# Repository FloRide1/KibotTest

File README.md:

# Kibot Test
## By Florian "FloRide" Reimat

## About
This repo is a test about a Kicad Plugins named "[KiBot](https://github.com/INTI-CMNB/kibot)", an all in one plugins made for automatically generate export files like BOM / Cost / Gerber / etc... It also handle CI / CD with Github / Gitlab.

## Images:
### Schematic:

### PCB:
| Front | Bottom |
:------:|:-------:
|| |
### 3D:
| Front | Bottom |
:------:|:-------:
|| |
| Tilted 1 | Tilted 2 |
|  |  |

## Others:
- [Interactive BOM](Export/ibom/KibotTest-ibom.html)
- [BOM](Export/bom/KibotTest-bom.csv)
- [Cost](Export/cost/KibotTest-kicost.xlsx)

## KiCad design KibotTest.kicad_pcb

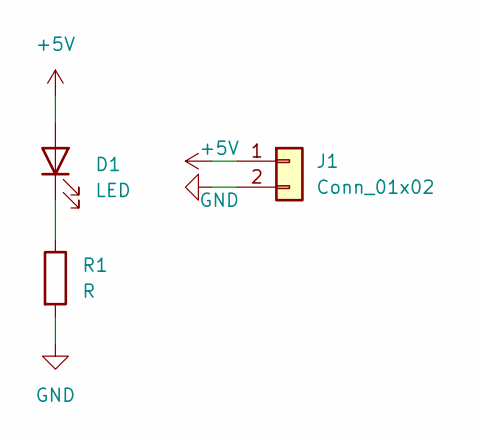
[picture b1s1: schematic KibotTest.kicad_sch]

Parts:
D1: LED; LED_0805_2012Metric
J1: Conn_01x02; JST_EH_B2B-EH-A_1x02_P2.50mm_Vertical
R1: R; R_0805_2012Metric_Pad1.20x1.40mm_HandSolder

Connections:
+5V: D1.2 (A), J1.1
GND: J1.2, R1.2
unnamed: D1.1 (K), R1.1

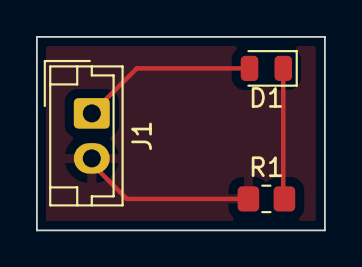
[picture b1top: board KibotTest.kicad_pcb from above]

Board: 2 copper layers, 16.0 x 10.8 mm, 3 parts (0 on the bottom side), 3 nets.

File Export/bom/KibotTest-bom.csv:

Row,Description,Part,References,Value,Footprint,Quantity Per PCB,Status,Datasheet
1,Light emitting diode,LED,D1,LED,LED_0805_2012Metric,1, ,~
2,"Generic connector, single row, 01x02, script generated (kicad-library-utils/schlib/autogen/connector/)",Conn_01x02,J1,Conn_01x02,JST_EH_B2B-EH-A_1x02_P2.50mm_Vertical,1, ,~
3,Resistor,R,R1,0 Ω,R_0805_2012Metric_Pad1.20x1.40mm_HandSolder,1, ,~





Project info:
Schematic:,KibotTest
Variant:,default
Revision:,
Date:,2022-06-05_00-02-45
KiCad Version:,6.0.4+dfsg-1~bpo11+1
Statistics:
Component Groups:,3
Component Count:,3
Fitted Components:,3
Number of PCBs:,1
Total Components:,3

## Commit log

2022-06-04 [INIT] Simple Test
2022-06-05 [ROOT] Implement Github Actions + Fix README.md
    [FIX] Update README images
    [NEW] Add schematics
    [ACT] Try to use github actions
    [ACT] Move to the good folder
    [ACT] First test of action
    [GEN] Remove generated for test
2022-06-05 [CI] Auto-release exports files
2022-06-05 [ACT] Test error detection
2022-06-05 Revert "[ACT] Test error detection"
    This reverts commit 250b70cec5ef92d058678cda262f443f8b6e7f6b.
2022-06-05 [FIX] Compression take the good repository now
2022-06-05 [FIX] Retry fixing Gerber
2022-06-05 [FIX] gitignore
2022-09-04 [SRC] Try to move src files in src folder
2022-09-04 [STYLE] Apply conding style on main.yaml
2022-09-04 [ACT] Test modify src path
2022-09-04 [ACT] Retry fixing path
2022-09-04 [ACT] Revert to working
2022-09-04 [ACT] Move .kicad_pro to the root of the project
2022-09-04 [ACT] New Test
2022-09-04 [CONF] Remove ** in /Gerber/
2022-09-04 [STYLE] Apply conding style on config.mail.yaml
2022-09-10 [ROOT] Remove src folder
2022-09-10 [CI/CD] Reiterate
2022-09-10 [CI/CD] Test
2022-09-10 [KICOST] Temporary disable it (it break the CI)
